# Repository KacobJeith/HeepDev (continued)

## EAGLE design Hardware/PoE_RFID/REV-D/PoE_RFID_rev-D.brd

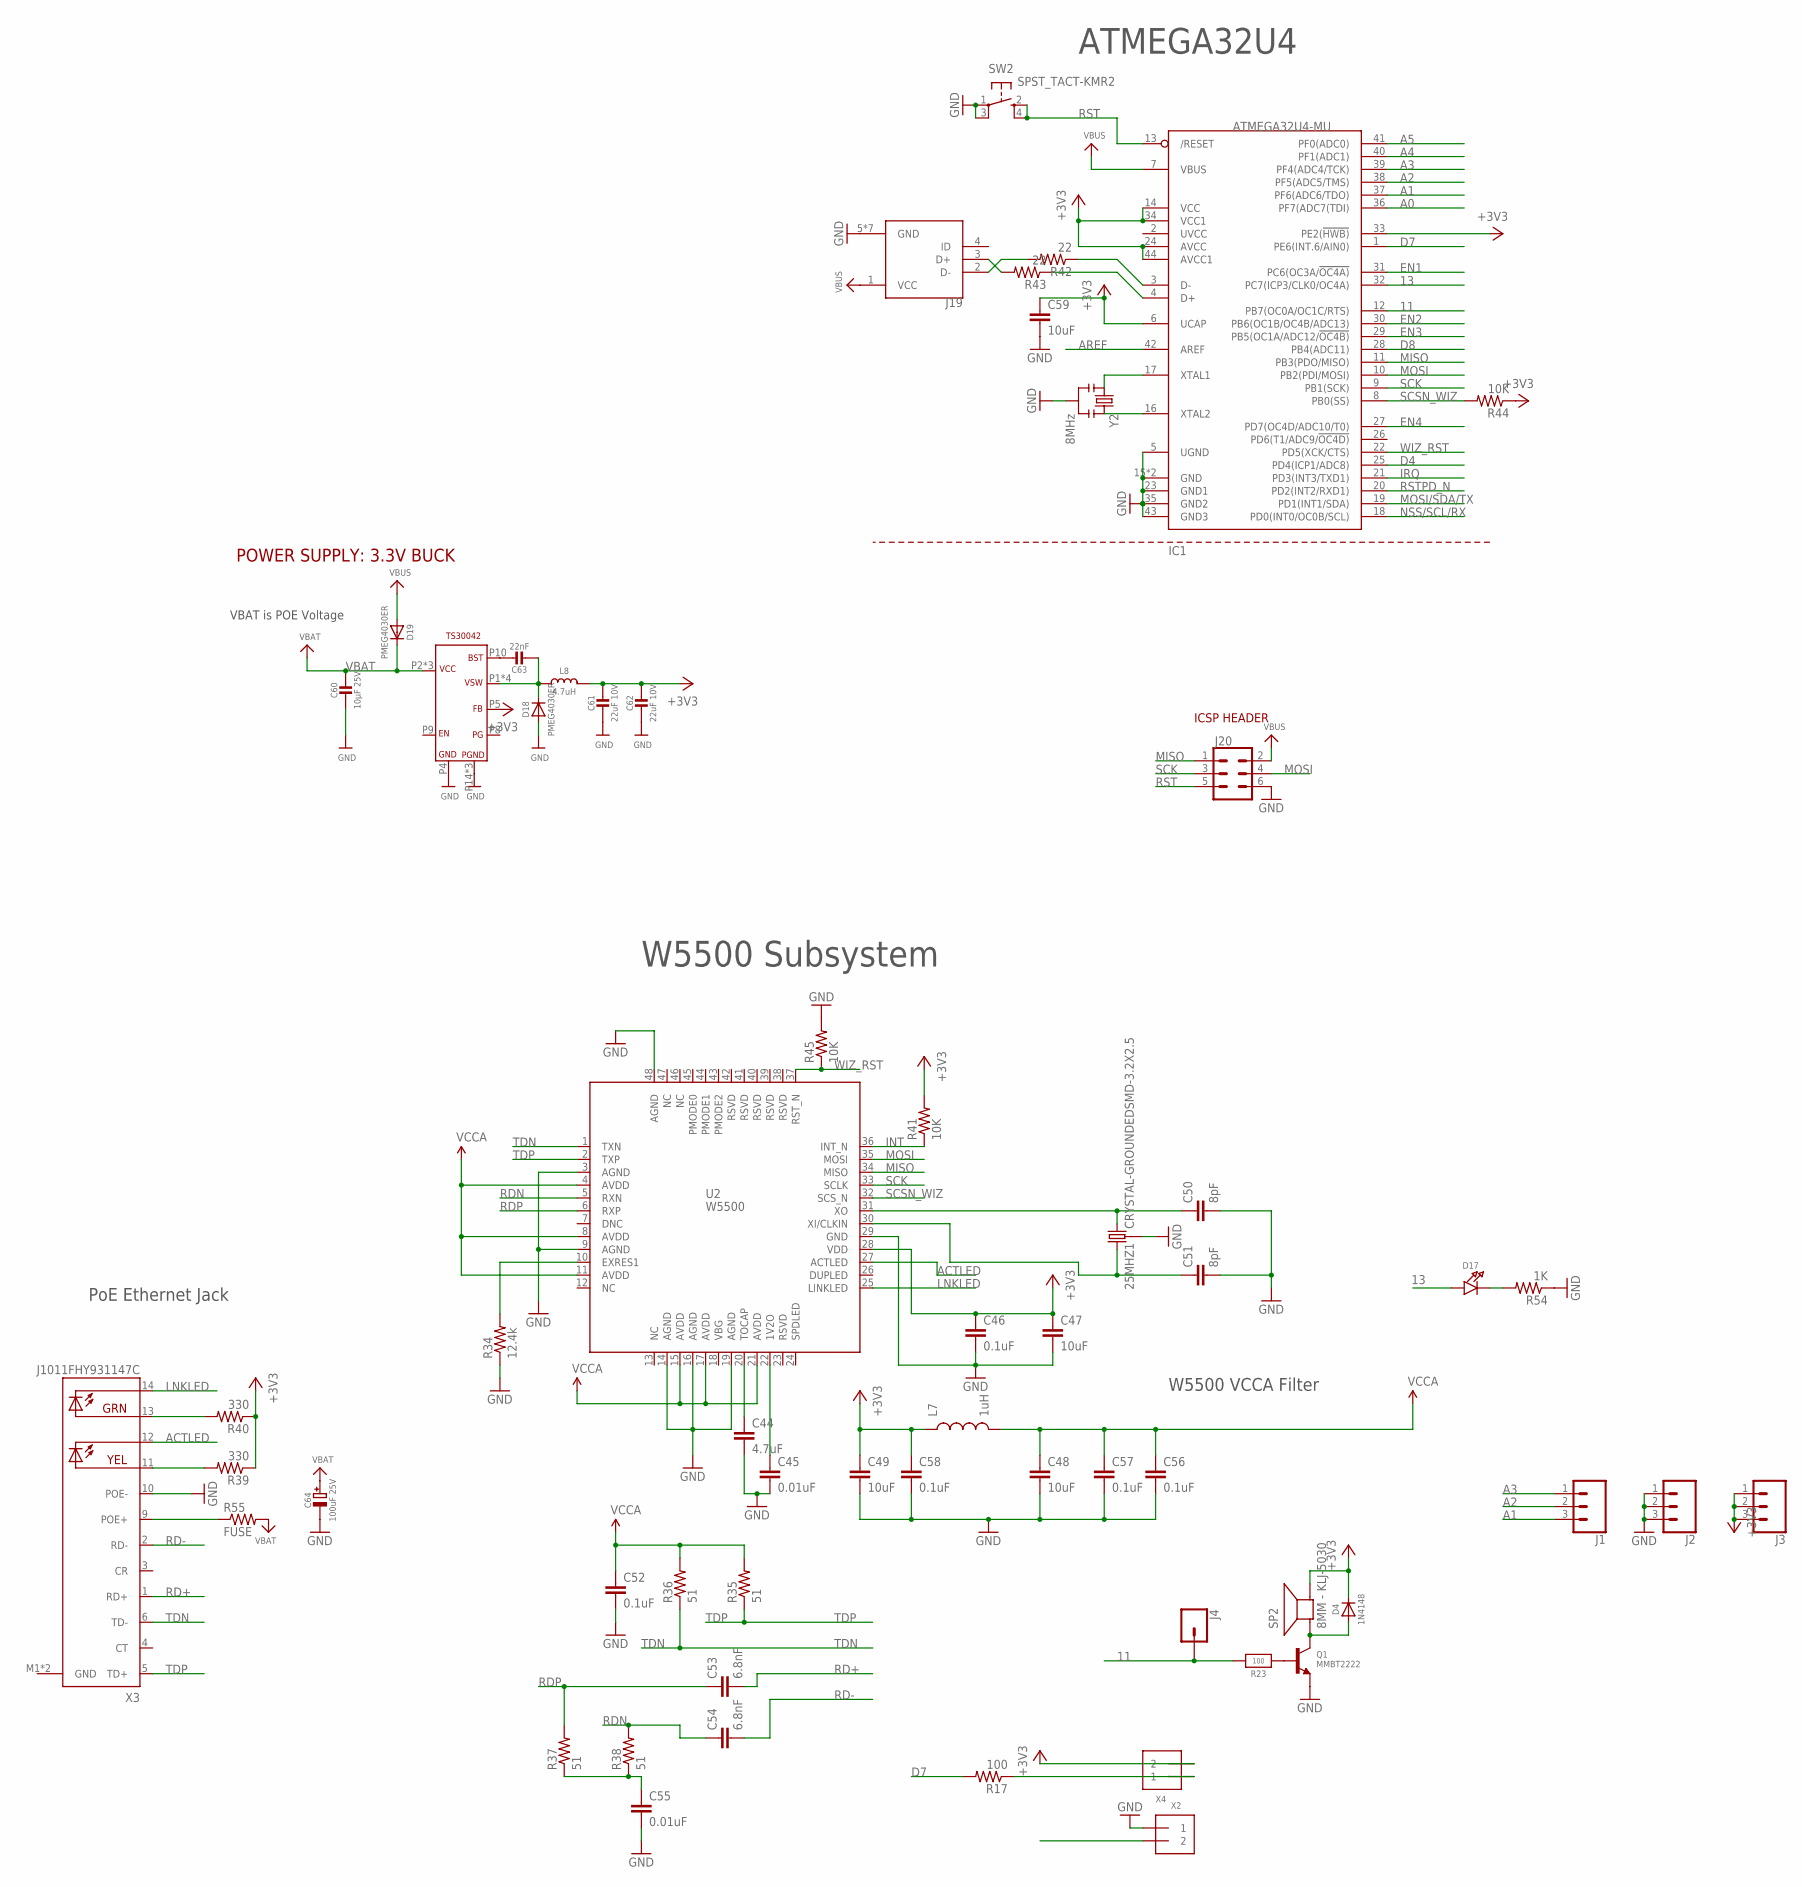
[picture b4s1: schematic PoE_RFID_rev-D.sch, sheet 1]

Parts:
25MHZ1: CRYSTAL-GROUNDEDSMD-3.2X2.5; CRYSTAL-SMD-3.2X2.5MM
C44: 4.7uF; 0603-CAP
C45, C55: 0.01uF; 0603-CAP
C46, C52, C56, C57, C58: 0.1uF; 0603-CAP
C47, C48, C49, C59: 10uF; 0603-CAP
C50, C51: 8pF; 0603-CAP
C53, C54: 6.8nF; 0603-CAP
C60: 10µF 25V; 0603-MINI
C61, C62: 22uF 10V; 0603-MINI
C63: 22nF; 0603-MINI
C64: 100uF 25V; PANASONIC_D
D4: 1N4148; SOD-323
D17: LED0805_NOOUTLINE; CHIPLED_0805_NOOUTLINE
D18, D19: PMEG4030ER; SOD-123
IC1: ATMEGA32U4-MU; TQFN44_7MM
J1: CONN_031X03_NO_SILK; 1X03_NO_SILK
J2, J3: CONN_03; 1X03
J4: CONN_01; 1X01
J19: 10103594-0001LF; FCI_10103594-0001LF
J20: CONN_03X2NO_SILK; 2X3-NS
L7: 1uH; 0603
L8: 4.7uH; INDUCTOR_5X5MM_TDK_VLC5045
Q1: MMBT2222; SOT23-WIDE
R17: 100; 0603-RES
R23: 100; 0603-NO@1
R34: 12.4k; 0603-RES
R35, R36, R37, R38: 51; 0603-RES
R39, R40: 330; 0603-RES
R41, R44, R45: 10K; 0603-RES
R42, R43: 22; 0603-RES
R54: 1K; 0603-RES
R55: FUSE; 0603-RES
SP2: 8MM - KLJ-5030; BUZZER_SMT_5MM
SW2: SPST_TACT-KMR2; KMR2
U2: W5500
U$55: BUCK_CONVERTER; QFN-16
X2, X4: TERMBLOCK_1X2; TERMBLOCK_1X2-3.5MM
X3: J1011FHY931147C; HANRUN_POE
Y2: 8MHz; RESONATOR-SMD

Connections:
11: IC1.12 (PB7(OC0A/OC1C/RTS)), J4.1, R23.2
13: D17.A, IC1.32 (PC7(ICP3/CLK0/OC4A))
+3V3: C46.1, C47.1, C49.1, C58.1, C59.1, C61.1, C62.1, D4.C, IC1.6 (UCAP), IC1.14 (VCC), IC1.24 (AVCC), IC1.33 (PE2(!HWB)), IC1.34 (VCC1), IC1.44 (AVCC1), J3.1, J3.2, J3.3, L7.1, L8.P$2 (2), R39.1, R40.1, R41.2, R44.1, SP2.-, U2.28 (VDD), U$55.P5 (FB), X2.2; also elsewhere on the board
A0: IC1.36 (PF7(ADC7(TDI))
A1: IC1.37 (PF6(ADC6/TDO)), J1.3
A2: IC1.38 (PF5(ADC5/TMS)), J1.2
A3: IC1.39 (PF4(ADC4/TCK)), J1.1
A4: IC1.40 (PF1(ADC1))
A5: IC1.41 (PF0(ADC0))
ACTLED: U2.27 (ACTLED), X3.12 (YEL-C)
AREF: IC1.42 (AREF)
D4: IC1.25 (PD4(ICP1/ADC8))
D7: IC1.1 (PE6(INT.6/AIN0)), R17.2
D8: IC1.28 (PB4(ADC11))
D+1: IC1.4 (D+), R43.1
D-1: IC1.3 (D-), R42.1
EN1: IC1.31 (PC6(OC3A/!OC4A)), X4.2
EN2: IC1.30 (PB6(OC1B/OC4B/ADC13))
EN3: IC1.29 (PB5(OC1A/ADC12/!OC4B))
EN4: IC1.27 (PD7(OC4D/ADC10/T0))
GND: 25MHZ1.2 (3), 25MHZ1.4 (3), C44.2, C45.2, C46.2, C47.2, C48.2, C49.2, C50.2, C51.2, C52.2, C55.2, C56.2, C57.2, C58.2, C59.2, C60.2, C61.2, C62.2, C64.-, D18.A, IC1.5 (UGND), IC1.15 (GND), IC1.23 (GND1), IC1.35 (GND2), IC1.43 (GND3), IC1.THERMAL (GND), J2.1, J2.2, J2.3, J19.5 (GND), J19.P1 (GND), J19.P2 (GND), J19.P3 (GND), J19.P4 (GND), J19.P5 (GND), J19.P6 (GND), J20.6, Q1.2 (E), R34.1, R45.2, R54.1, SW2.1, SW2.3 (P1), U2.3 (AGND), U2.9 (AGND), U2.14 (AGND), U2.16 (AGND), U2.19 (AGND), U2.29 (GND), U2.48 (AGND), U$55.P4 (GND), U$55.P14 (PGND), U$55.P15 (PGND), U$55.PAD (PGND), X3.10 (POE-), X3.M1 (GND), X3.M2 (GND), X4.1, Y2.2; also elsewhere on the board
INT: R41.1, U2.36 (INT_N)
IRQ: IC1.21 (PD3(INT3/TXD1)); also elsewhere on the board
LNKLED: U2.25 (LINKLED), X3.14 (GRN-C)
MISO: IC1.11 (PB3(PDO/MISO)), J20.1, U2.34 (MISO)
MOSI: IC1.10 (PB2(PDI/MOSI)), J20.4, U2.35 (MOSI)
MOSI/SDA/TX: IC1.19 (PD1(INT1/SDA)); also elsewhere on the board
unnamed: R17.1, X2.1
unnamed: Q1.1 (B), R23.1
unnamed: D4.A, Q1.3 (C), SP2.+
unnamed: C44.1, U2.20 (TOCAP)
unnamed: C45.1, U2.22 (1V2O)
unnamed: R34.2, U2.10 (EXRES1)
unnamed: C55.1, R37.1, R38.1
unnamed: 25MHZ1.3 (2), C50.1, U2.31 (XO)
unnamed: 25MHZ1.1, C51.1, U2.30 (XI/CLKIN)
unnamed: IC1.16 (XTAL2), Y2.3
unnamed: IC1.17 (XTAL1), Y2.1
unnamed: J19.3 (D+), R43.2
unnamed: J19.2 (D-), R42.2
unnamed: D17.C, R54.2
unnamed: R40.2, X3.13 (GRN-A)
unnamed: R39.2, X3.11 (YEL-A)
unnamed: C63.1, U$55.P10 (BST)
unnamed: C63.2, D18.C, L8.P$1 (1), U$55.P1 (VSW), U$55.P12 (VSW), U$55.P13 (VSW), U$55.P16 (VSW)
unnamed: R55.1, X3.9 (POE+)
NSS/SCL/RX: IC1.18 (PD0(INT0/OC0B/SCL)); also elsewhere on the board
RD+: C53.2, X3.1 (RD+)
RD-: C54.2, X3.2 (RD-)
RDN: C54.1, R38.2, U2.5 (RXN)
RDP: C53.1, R37.2, U2.6 (RXP)
RST: IC1.13 (/RESET), J20.5, SW2.2 (S), SW2.4 (S1)
RSTPD_N: IC1.20 (PD2(INT2/RXD1)); also elsewhere on the board
SCK: IC1.9 (PB1(SCK)), J20.3, U2.33 (SCLK)
SCSN_WIZ: IC1.8 (PB0(SS)), R44.2, U2.32 (SCS_N)
TDN: R36.1, U2.1 (TXN), X3.6 (TD-)
TDP: R35.1, U2.2 (TXP), X3.5 (TD+)
VBAT: C60.1, C64.+, D19.C, R55.2, U$55.P2 (VCC), U$55.P3 (VCC), U$55.P11 (VCC)
VBUS: D19.A, IC1.7 (VBUS), J19.1 (VCC), J20.2
VCCA: C48.1, C52.1, C56.1, C57.1, L7.2, R35.2, R36.2, U2.4 (AVDD), U2.8 (AVDD), U2.11 (AVDD), U2.15 (AVDD), U2.17 (AVDD), U2.21 (AVDD)
WIZ_RST: IC1.22 (PD5(XCK/CTS)), R45.1, U2.37 (RST_N)

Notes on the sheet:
W5500 Subsystem
W5500 VCCA Filter
PoE Ethernet Jack
ATMEGA32U4
ICSP HEADER
POWER SUPPLY: 3.3V BUCK
VBAT is POE Voltage

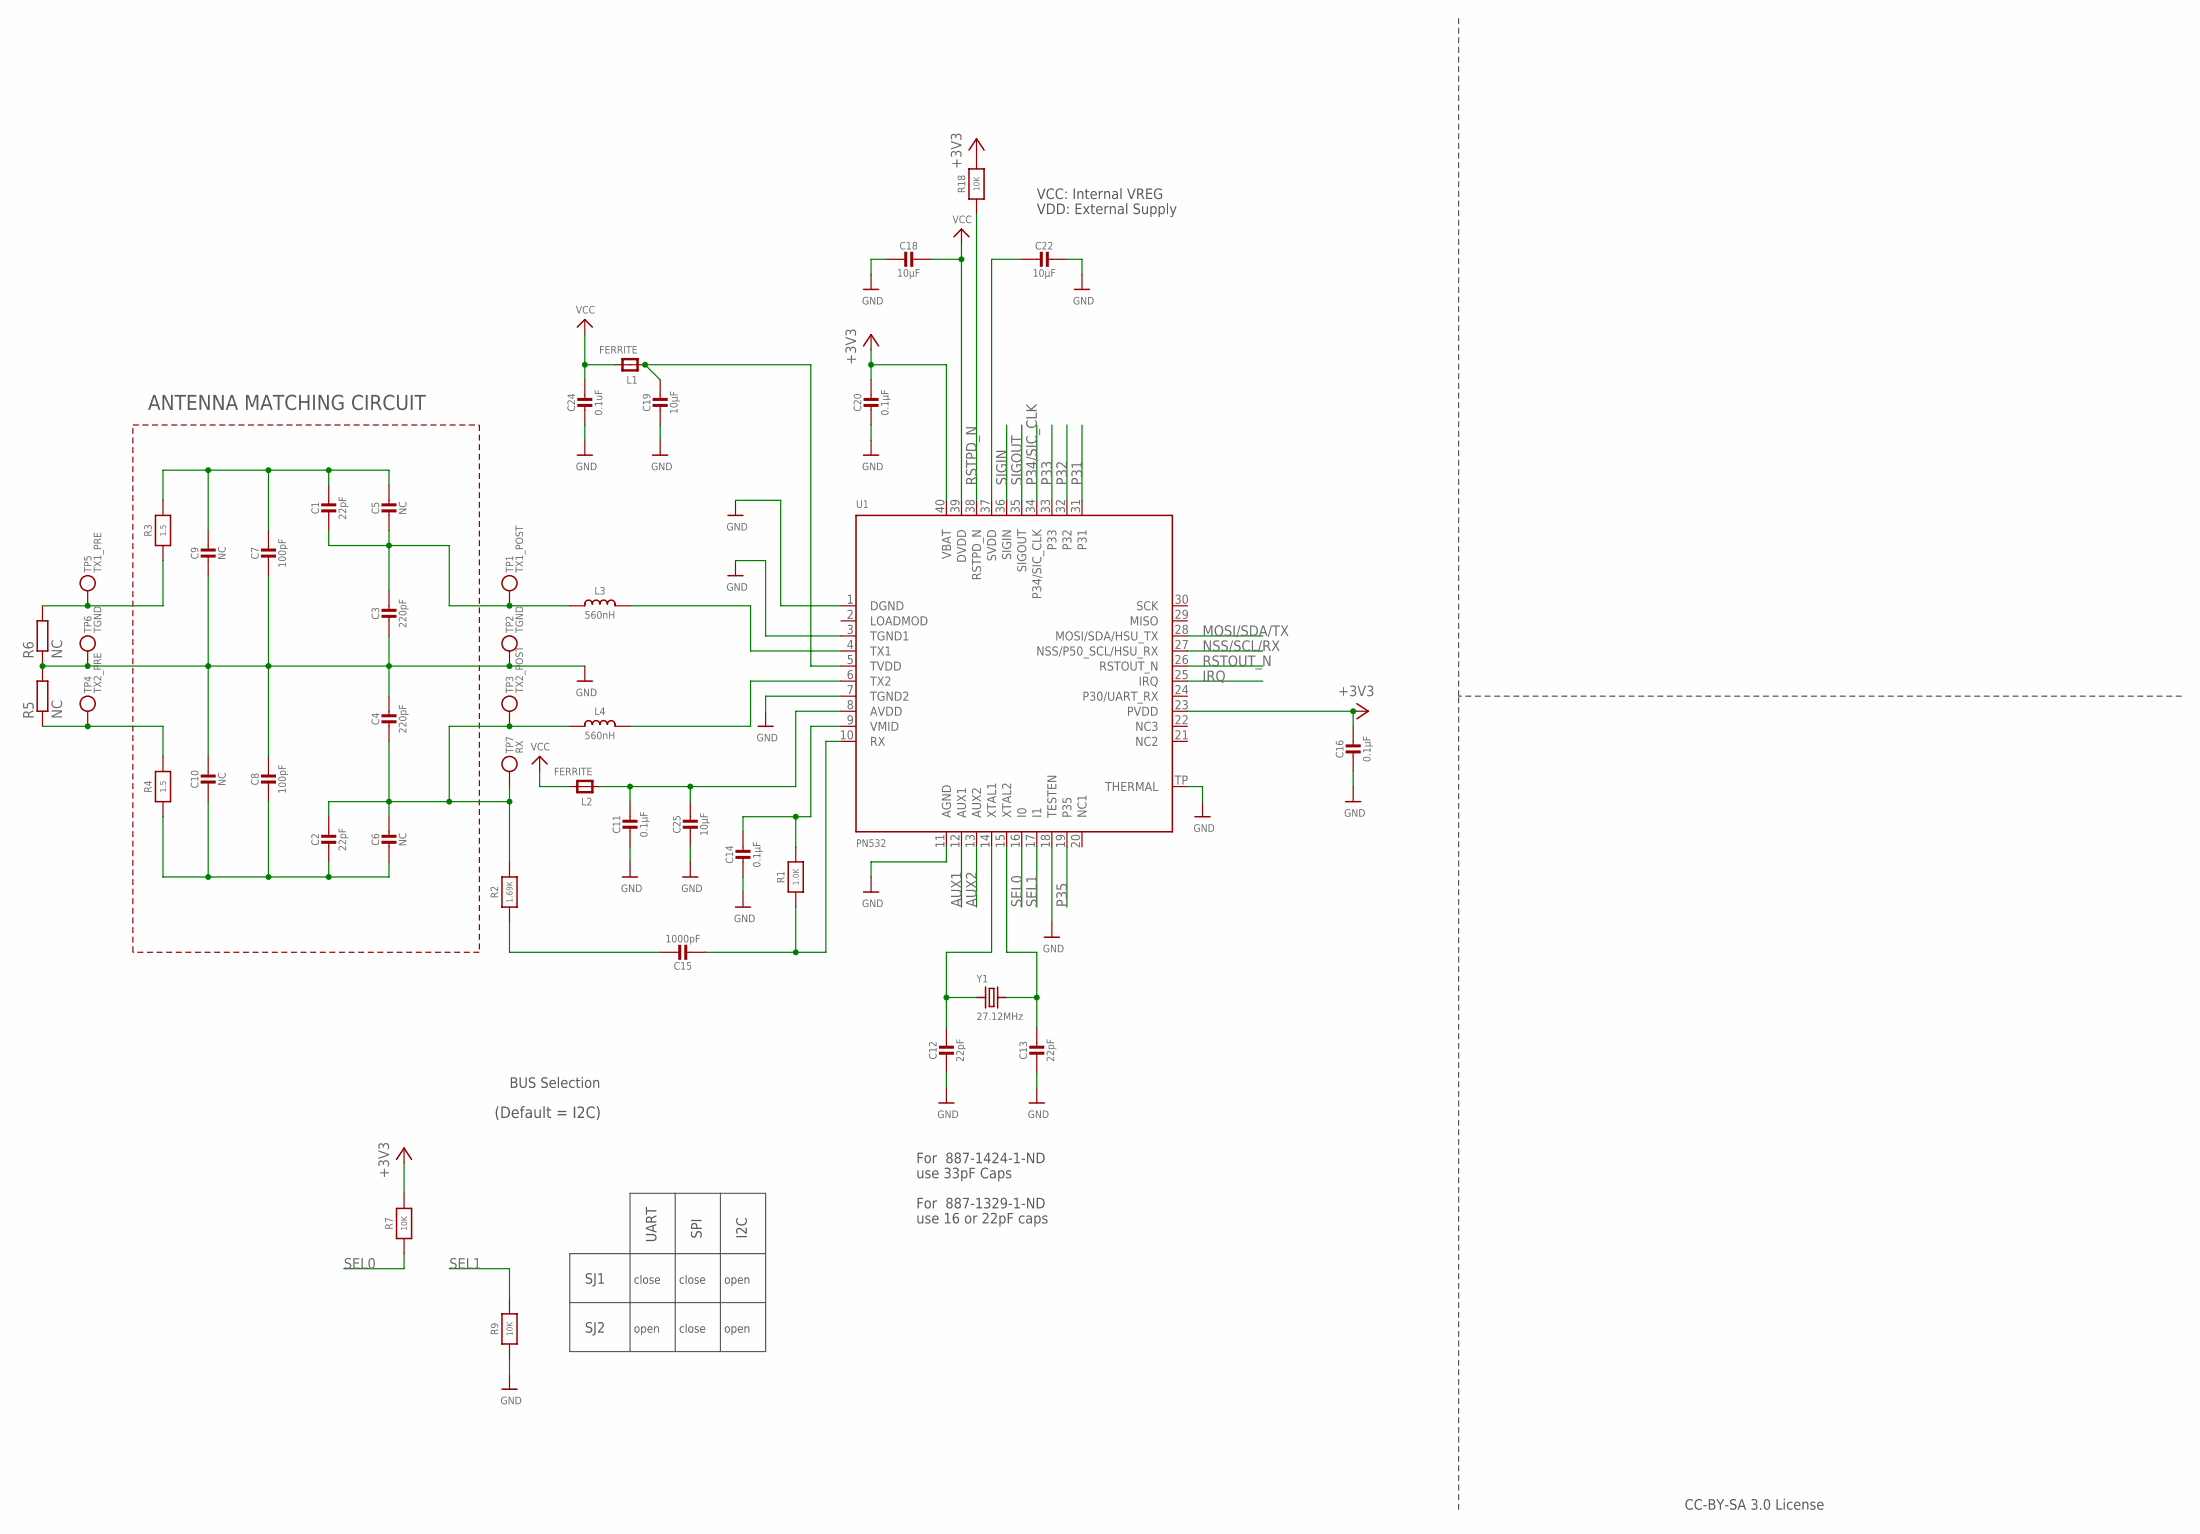
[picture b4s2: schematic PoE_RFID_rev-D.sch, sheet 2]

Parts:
C1, C2, C12, C13: 22pF; 0603-NO
C3, C4: 220pF; 0603-NO
C5, C6, C9, C10: NC; 0603-NO
C7, C8: 100pF; 0603-NO
C11, C14, C16, C20: 0.1µF; 0603-NO
C15: 1000pF; 0603-NO
C18, C19, C22, C25: 10µF; 0603-NO
C24: 0.1uF; 0603-NO
L1, L2: FERRITE; _0603
L3, L4: 560nH; 0603-NO
R1: 1.0K; 0603-NO@1
R2: 1.69K; 0603-NO@1
R3, R4: 1.5; 0603-NO@1
R5, R6: NC; R0201
R7, R9, R18: 10K; 0603-NO@1
TP1: TX1_POST; PAD-1.5X2.0
TP2, TP6: TGND; PAD-1.5X2.0
TP3: TX2_POST; PAD-1.5X2.0
TP4: TX2_PRE; PAD-1.5X2.0
TP5: TX1_PRE; PAD-1.5X2.0
TP7: RX; PAD-1.5X2.0
U1: PN532; HVQFN40-6X6
Y1: 27.12MHz; CRYSTAL_3.2X2.5

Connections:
+3V3: C16.1, C20.1, R7.2, R18.2, U1.23 (PVDD), U1.40 (VBAT); also elsewhere on the board
AUX1: U1.12 (AUX1)
AUX2: U1.13 (AUX2)
GND: C3.2, C4.1, C7.2, C8.1, C9.2, C10.1, C11.2, C12.2, C13.2, C14.2, C16.2, C18.2, C19.2, C20.2, C22.1, C24.2, C25.2, R5.2, R6.1, R9.1, TP2.P$1, TP6.P$1, U1.1 (DGND), U1.3 (TGND1), U1.7 (TGND2), U1.11 (AGND), U1.18 (TESTEN), U1.TP (THERMAL); also elsewhere on the board
IRQ: U1.25 (IRQ); also elsewhere on the board
MOSI/SDA/TX: U1.28 (MOSI/SDA/HSU_TX); also elsewhere on the board
unnamed: L3.2, U1.4 (TX1)
unnamed: L4.2, U1.6 (TX2)
unnamed: C1.2, C3.1, C5.2, L3.1, TP1.P$1
unnamed: R3.1, R6.2, TP5.P$1
unnamed: R4.2, R5.1, TP4.P$1
unnamed: C12.1, U1.14 (XTAL1), Y1.1
unnamed: C13.1, U1.15 (XTAL2), Y1.2
unnamed: C15.1, R2.1
unnamed: C14.1, R1.2, U1.9 (VMID)
unnamed: C15.2, R1.1, U1.10 (RX)
unnamed: C2.1, C4.2, C6.1, L4.1, R2.2, TP3.P$1, TP7.P$1
unnamed: C11.1, C25.1, L2.1, U1.8 (AVDD)
unnamed: C19.1, L1.1, U1.5 (TVDD)
unnamed: C22.2, U1.37 (SVDD)
NSS/SCL/RX: U1.27 (NSS/P50_SCL/HSU_RX); also elsewhere on the board
P31: U1.31
P32: U1.32
P33: U1.33
P34/SIC_CLK: U1.34 (P34/SIC_CLK)
P35: U1.19 (P35)
RSTOUT_N: U1.26 (RSTOUT_N)
RSTPD_N: R18.1, U1.38 (RSTPD_N); also elsewhere on the board
SEL0: R7.1, U1.16 (I0)
SEL1: R9.2, U1.17 (I1)
SIGIN: U1.36 (SIGIN)
SIGOUT: U1.35 (SIGOUT)
TX1_ANTENNA: C1.1, C5.1, C7.1, C9.1, R3.2
TX2_ANTENNA: C2.2, C6.2, C8.2, C10.2, R4.1
VCC: C18.1, C24.1, L1.2, L2.2, U1.39 (DVDD)

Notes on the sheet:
ANTENNA MATCHING CIRCUIT
SJ1
SJ2
UART
SPI
I2C
close
open
CC-BY-SA 3.0 License
For 887-1329-1-ND
use 16 or 22pF caps
For 887-1424-1-ND
use 33pF Caps
BUS Selection
(Default = I2C)
VCC: Internal VREG
VDD: External Supply

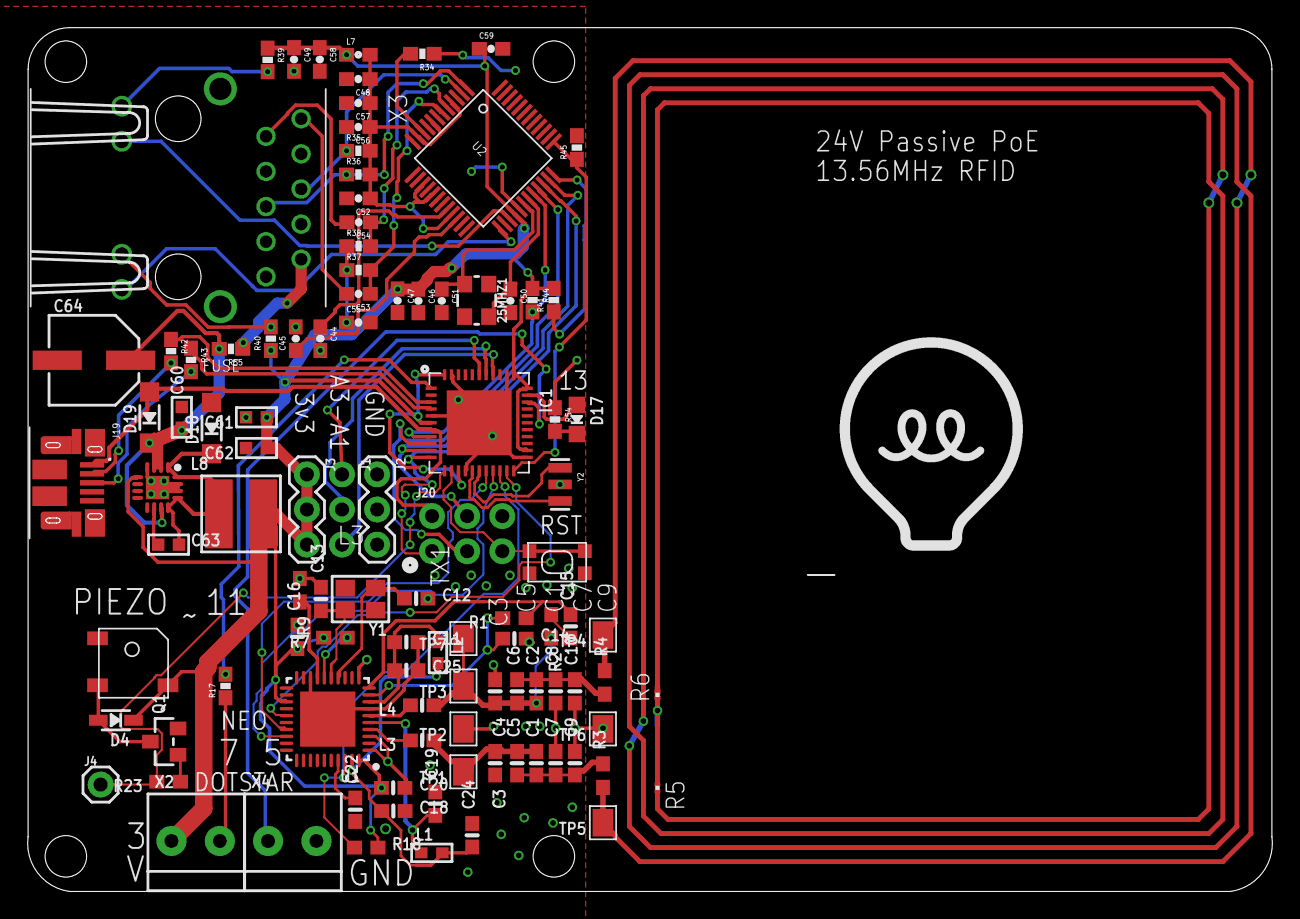
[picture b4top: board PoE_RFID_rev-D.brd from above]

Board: 2 copper layers, 90.0 x 62.5 mm, 105 parts (0 on the bottom side), 71 nets.

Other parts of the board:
U$19: HEEPLOGO

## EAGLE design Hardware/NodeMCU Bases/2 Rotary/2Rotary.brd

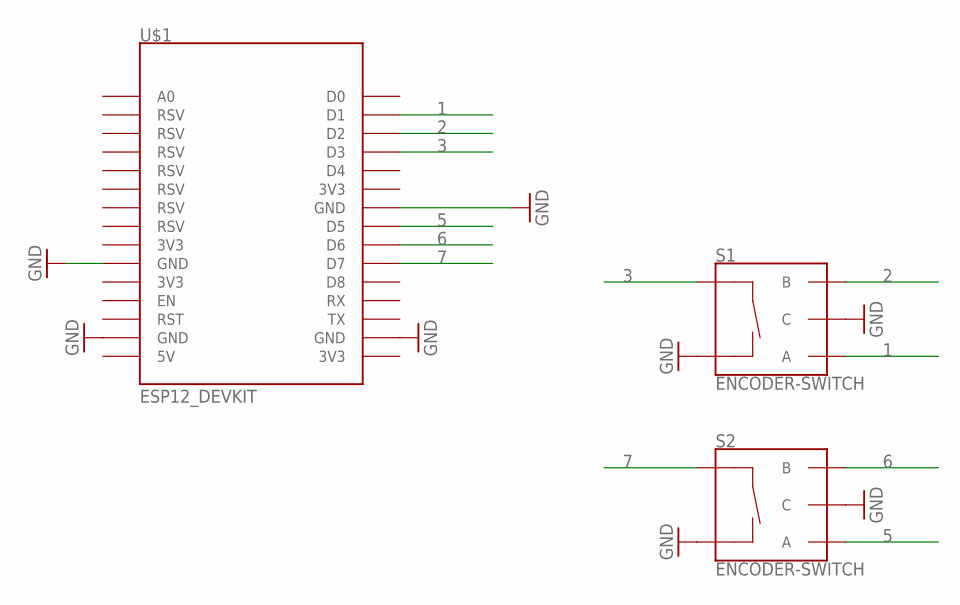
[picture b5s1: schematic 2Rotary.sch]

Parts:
S1, S2: ENCODER-SWITCH; ROTARY_ENC_PLAIN
U$1: ESP12_DEVKIT

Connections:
1: S1.A, U$1.D1
2: S1.B, U$1.D2
3: S1.SW+, U$1.D3
5: S2.A, U$1.D5
6: S2.B, U$1.D6
7: S2.SW+, U$1.D7
GND: S1.C, S1.SW-, S2.C, S2.SW-, U$1.GND@0 (GND), U$1.GND@1 (GND), U$1.GND@2 (GND), U$1.GND@3 (GND)

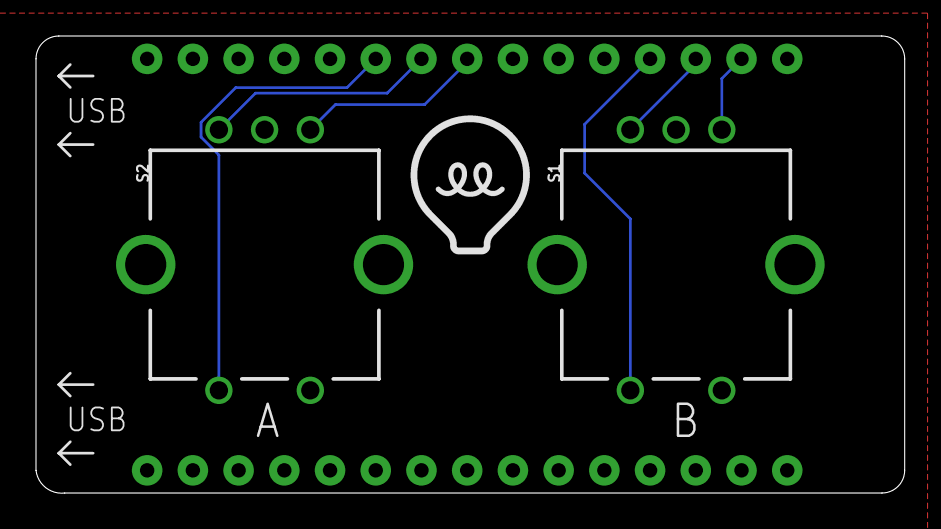
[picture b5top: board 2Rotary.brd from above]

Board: 2 copper layers, 48.3 x 25.4 mm, 4 parts (1 on the bottom side), 7 nets.

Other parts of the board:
U$2: HEEPLOGOSMALL

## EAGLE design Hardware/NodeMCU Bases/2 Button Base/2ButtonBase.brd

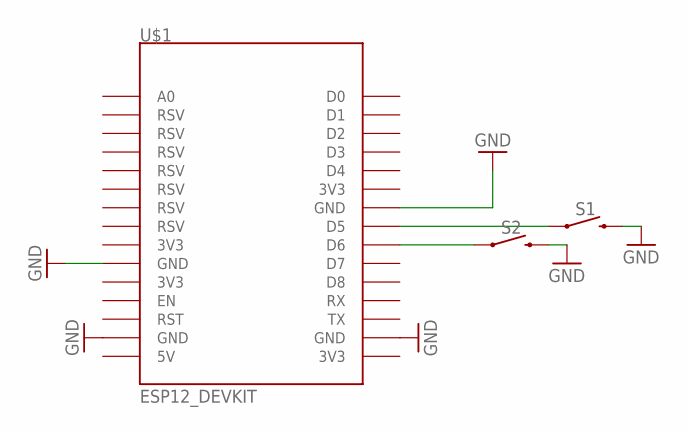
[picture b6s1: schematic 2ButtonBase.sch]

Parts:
S1, S2: MOMENTARY-SWITCH-SPST-PTH-12MM; TACTILE_SWITCH_PTH_12MM
U$1: ESP12_DEVKIT

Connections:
GND: S1.3 (2), S2.3 (2), U$1.GND@0 (GND), U$1.GND@1 (GND), U$1.GND@2 (GND), U$1.GND@3 (GND)
unnamed: S1.1, U$1.D5
unnamed: S2.1, U$1.D6

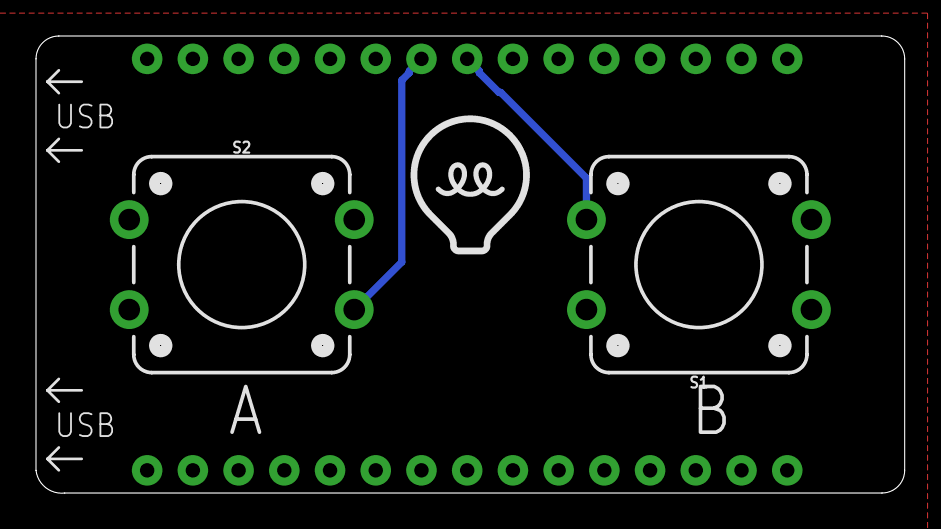
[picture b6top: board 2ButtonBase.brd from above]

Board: 2 copper layers, 48.3 x 25.4 mm, 4 parts (1 on the bottom side), 3 nets.

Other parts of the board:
U$2: HEEPLOGOSMALL

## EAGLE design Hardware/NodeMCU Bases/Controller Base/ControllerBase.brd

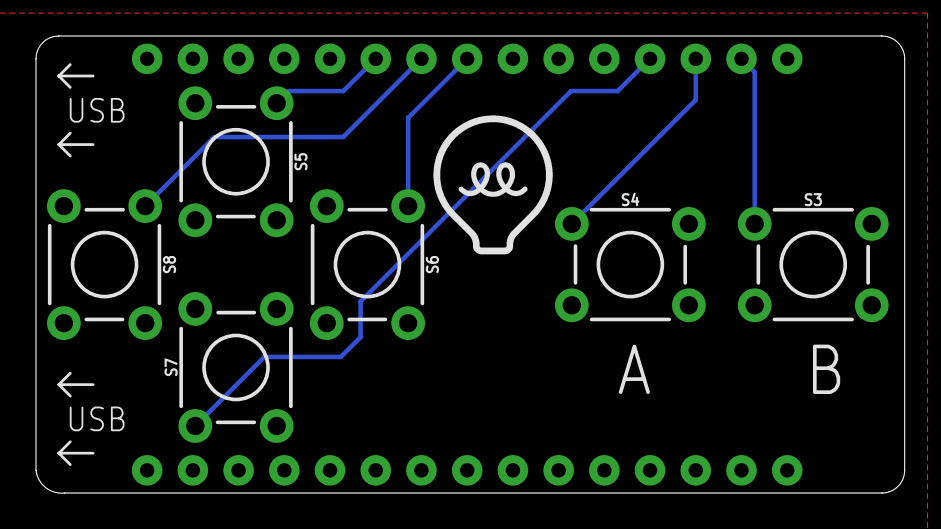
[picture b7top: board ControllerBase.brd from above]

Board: 2 copper layers, 48.3 x 25.4 mm, 8 parts (1 on the bottom side), 7 nets.

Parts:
S3, S4, S5, S6, S7, S8: TACTILE_SWITCH_PTH_6.0MM
U$1: ESP12_DEVKIT
U$2: HEEPLOGOSMALL

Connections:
1: S3.1, U$1.D1
2: S4.1, U$1.D2
3: S7.1, U$1.D3
5: S6.1, U$1.D5
6: S8.1, U$1.D6
7: S5.1, U$1.D7
GND: S3.3, S4.3, S5.3, S6.3, S7.3, S8.3, U$1.GND@0, U$1.GND@1, U$1.GND@2, U$1.GND@3

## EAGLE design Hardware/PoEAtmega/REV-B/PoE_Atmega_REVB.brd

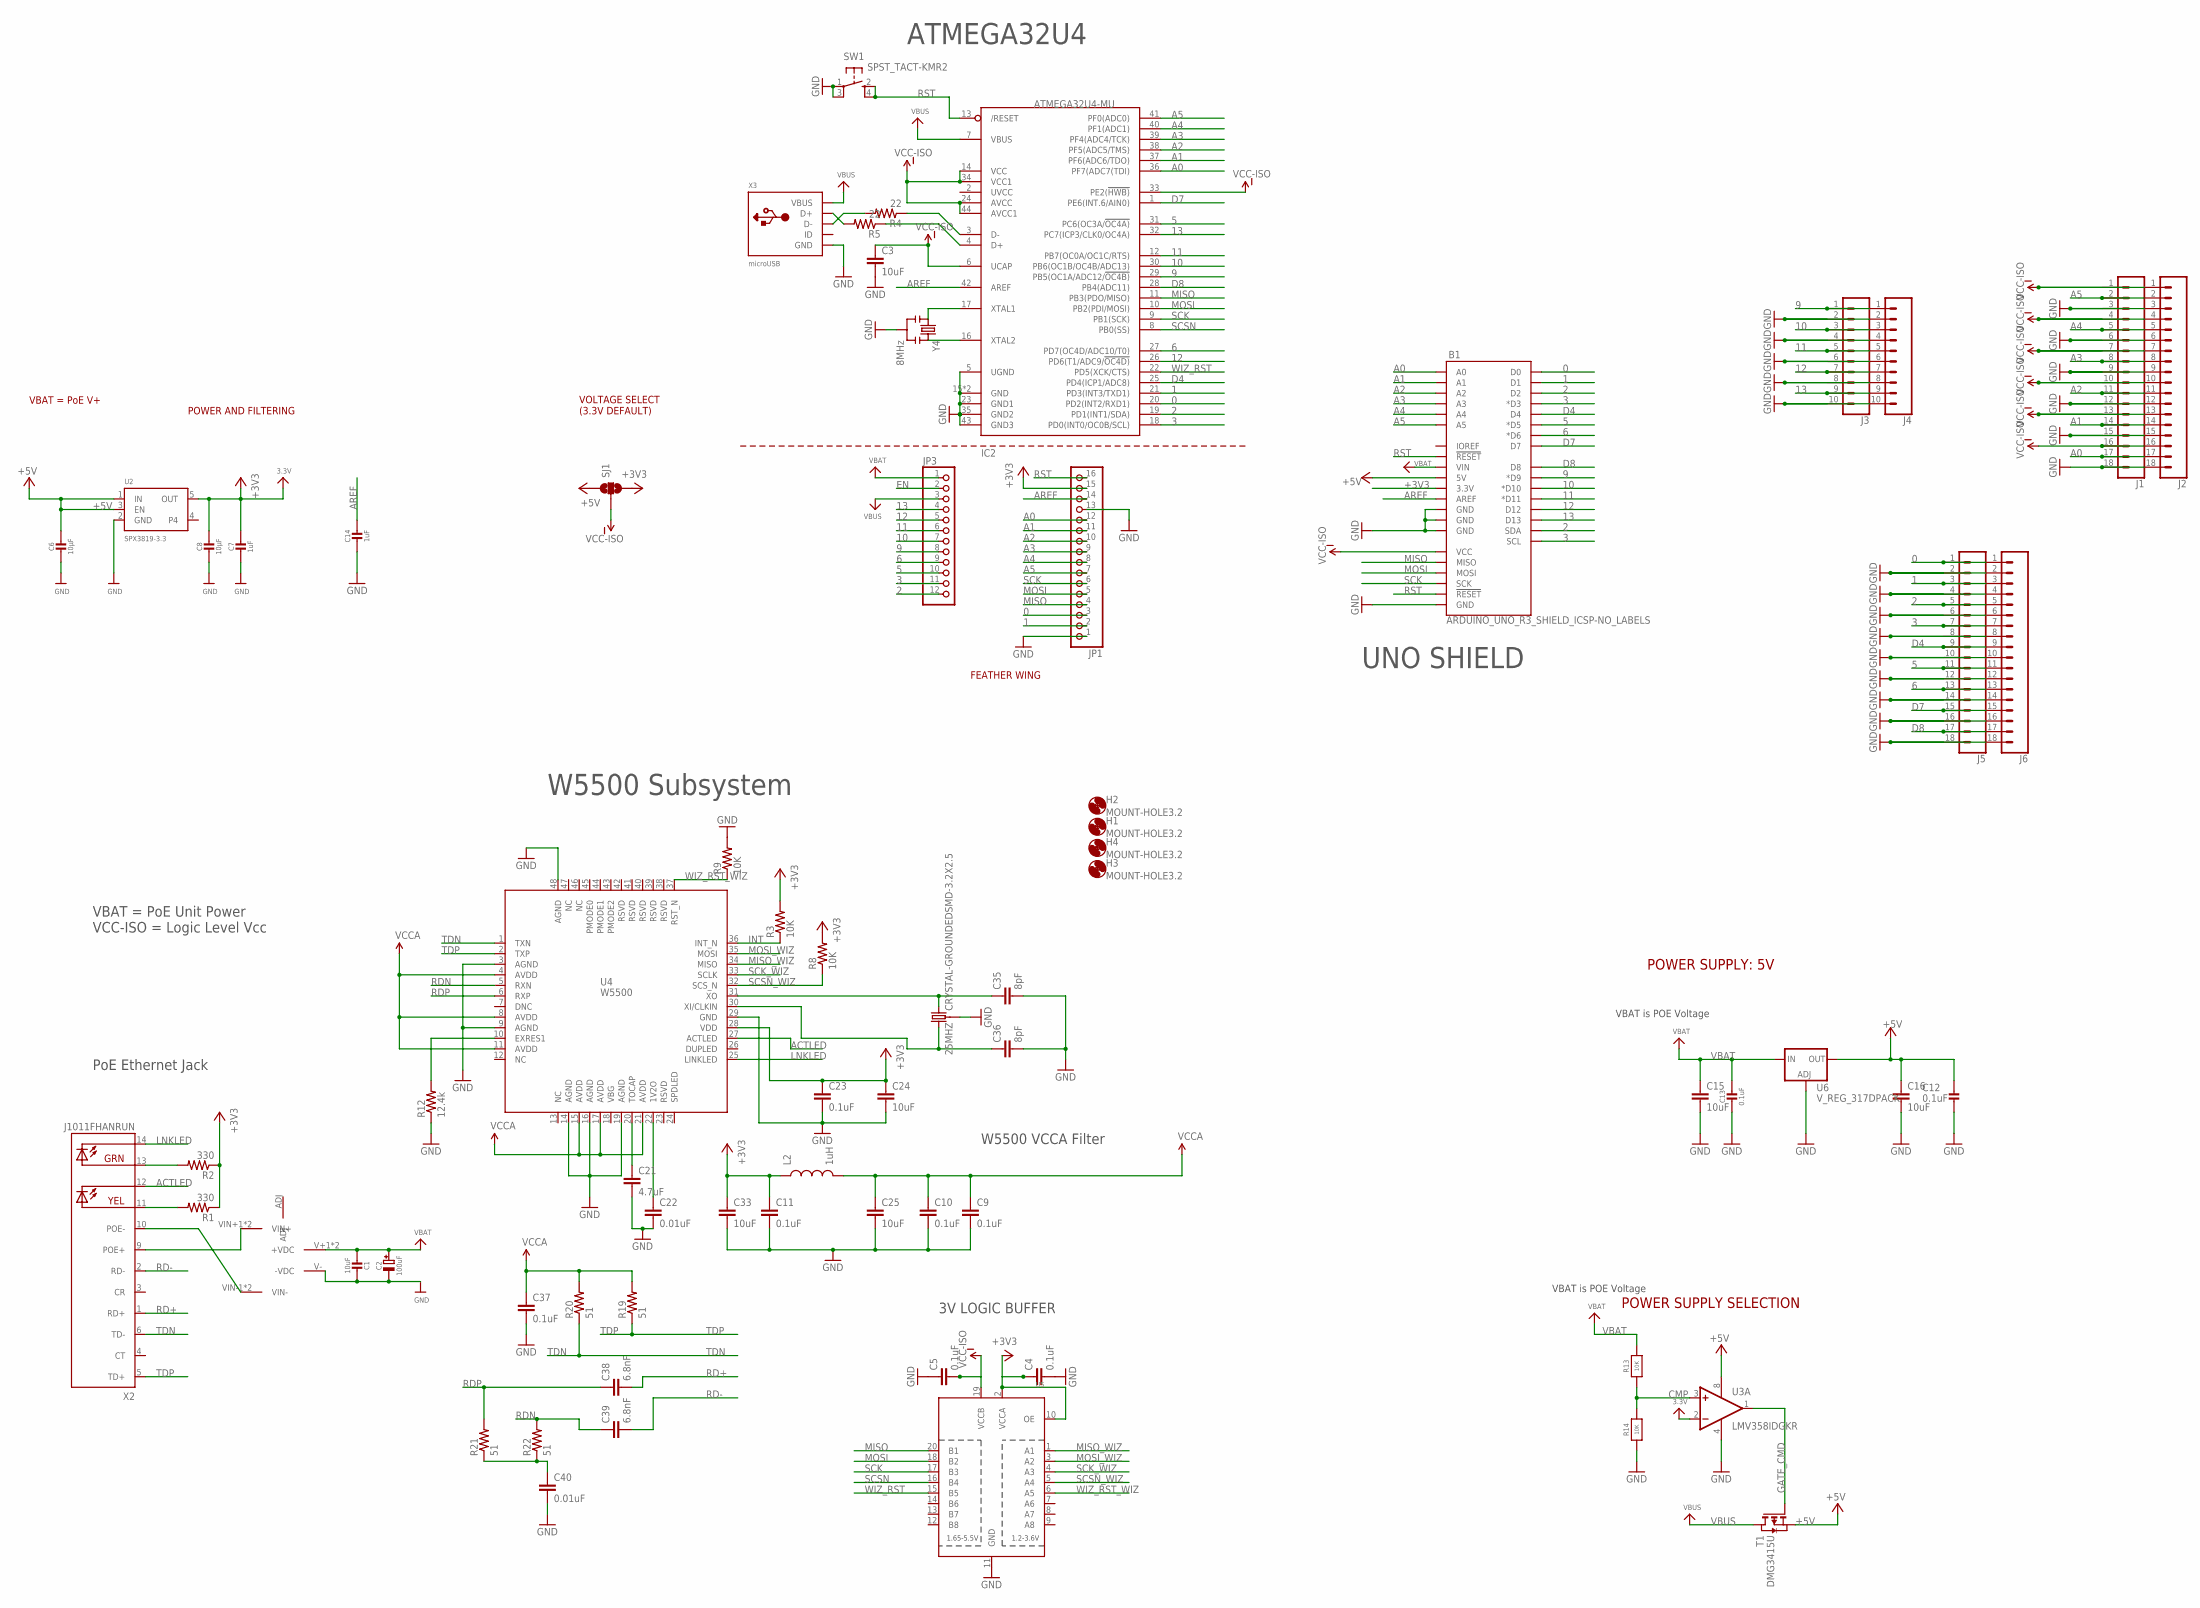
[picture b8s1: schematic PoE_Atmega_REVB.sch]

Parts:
25MHZ: CRYSTAL-GROUNDEDSMD-3.2X2.5; CRYSTAL-SMD-3.2X2.5MM
B1: ARDUINO_UNO_R3_SHIELD_ICSP-NO_LABELS; UNO_R3_SHIELD_ICSP_NOLABELS
C1: 10uF; _0805MP
C2: 100uF; PANASONIC_C
C3, C15, C16, C24, C25, C33: 10uF; 0603-CAP
C4, C5, C9, C10, C11, C23, C37: 0.1uF; 0603-CAP
C6, C8: 10µF; 0603-MINI
C7: 1uF; 0603-MINI
C12, C13: 0.1uF; 0805-NO
C14: 1uF; 0603-NO
C21: 4.7uF; 0603-CAP
C22, C40: 0.01uF; 0603-CAP
C35, C36: 8pF; 0603-CAP
C38, C39: 6.8nF; 0603-CAP
H1, H2, H3, H4: MOUNT-HOLE3.2; 3,2
IC2: ATMEGA32U4-MU; TQFN44_7MM
J1, J2, J5, J6: CONN_18; 1X18
J3, J4: CONN_10"; 1X10
JP1: HEADER-1X16ROUND; 1X16_ROUND
JP3: HEADER-1X12; 1X12_ROUND
L2: 1uH; 0603
R1, R2: 330; 0603-RES
R3, R8, R9: 10K; 0603-RES
R4, R5: 22; 0603-RES
R12: 12.4k; 0603-RES
R13, R14: 10K; 0805-NO
R19, R20, R21, R22: 51; 0603-RES
SJ1: SOLDERJUMPER_2WAYPASTE2&3; SJ_3_PASTE2&3
SW1: SPST_TACT-KMR2; KMR2
T1: DMG3415U; SOT-23
U2: SPX3819-3.3; SOT23-5
U3: LMV358IDGKR; MSOP08
U4: W5500
U5: TXB0108PWR; TSSOP20
U6: V_REG_317DPACK; V-REG_DPACK
U$1: SILVERTEL_POEMICRO; AG9900
X2: J1011FHANRUN; HANRUN_POE
X3: microUSB; 4UCONN_20329_V2
Y4: 8MHz; RESONATOR-SMD

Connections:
0: B1.RX (D0), IC2.20 (PD2(INT2/RXD1)), J5.1, J6.1, JP1.3
1: B1.TX (D1), IC2.21 (PD3(INT3/TXD1)), J5.3, J6.3, JP1.2
2: B1.D2, B1.SDA, IC2.19 (PD1(INT1/SDA)), J5.5, J6.5, JP3.12
3: B1.D3 (*D3), B1.SCL, IC2.18 (PD0(INT0/OC0B/SCL)), J5.7, J6.7, JP3.11
5: B1.D5 (*D5), IC2.31 (PC6(OC3A/!OC4A)), J5.11, J6.11, JP3.10
6: B1.D6 (*D6), IC2.27 (PD7(OC4D/ADC10/T0)), J5.13, J6.13, JP3.9
9: B1.D9 (*D9), IC2.29 (PB5(OC1A/ADC12/!OC4B)), J3.1, J4.1, JP3.8
10: B1.D10 (*D10), IC2.30 (PB6(OC1B/OC4B/ADC13)), J3.3, J4.3, JP3.7
11: B1.D11 (*D11), IC2.12 (PB7(OC0A/OC1C/RTS)), J3.5, J4.5, JP3.6
12: B1.D12, IC2.26 (PD6(T1/ADC9/!OC4D)), J3.7, J4.7, JP3.5
13: B1.D13, IC2.32 (PC7(ICP3/CLK0/OC4A)), J3.9, J4.9, JP3.4
+3V3: B1.3.3V, C4.1, C7.1, C8.1, C11.1, C23.1, C24.1, C33.1, JP1.15, L2.1, R1.1, R2.1, R3.2, R8.2, SJ1.3, U2.5 (OUT), U3.2 (-IN), U4.28 (VDD), U5.2 (VCCA), U5.10 (OE)
+5V: B1.5V, C6.1, C12.2, C16.1, SJ1.1, T1.2 (S), U2.1 (IN), U2.3 (EN), U3.8 (V+), U6.4 (OUT)
A0: B1.A0, IC2.36 (PF7(ADC7(TDI)), J1.17, J2.17, JP1.12
A1: B1.A1, IC2.37 (PF6(ADC6/TDO)), J1.14, J2.14, JP1.11
A2: B1.A2, IC2.38 (PF5(ADC5/TMS)), J1.11, J2.11, JP1.10
A3: B1.A3, IC2.39 (PF4(ADC4/TCK)), J1.8, J2.8, JP1.9
A4: B1.A4, IC2.40 (PF1(ADC1)), J1.5, J2.5, JP1.8
A5: B1.A5, IC2.41 (PF0(ADC0)), J1.2, J2.2, JP1.7
ACTLED: U4.27 (ACTLED), X2.12 (YEL-C)
AREF: B1.AREF, C14.1, IC2.42 (AREF), JP1.14
CMP: R13.1, R14.2, U3.3 (+IN)
D4: B1.D4, IC2.25 (PD4(ICP1/ADC8)), J5.9, J6.9
D7: B1.D7, IC2.1 (PE6(INT.6/AIN0)), J5.15, J6.15
D8: B1.D8, IC2.28 (PB4(ADC11)), J5.17, J6.17
D+: IC2.4 (D+), R5.1
D-: IC2.3 (D-), R4.1
EN: JP3.2
GATE_CMD: T1.3 (G), U3.1 (OUT)
GND: 25MHZ.2 (3), 25MHZ.4 (3), B1.GND@0 (GND), B1.GND@1 (GND), B1.GND@2 (GND), B1.GND_ICSP (GND), C1.1, C2.-, C3.2, C4.2, C5.1, C6.2, C7.2, C8.2, C9.2, C10.2, C11.2, C12.1, C13.2, C14.2, C15.2, C16.2, C21.2, C22.2, C23.2, C24.2, C25.2, C33.2, C35.2, C36.2, C37.2, C40.2, IC2.5 (UGND), IC2.15 (GND), IC2.23 (GND1), IC2.35 (GND2), IC2.43 (GND3), IC2.THERMAL (GND), J1.3, J1.6, J1.9, J1.12, J1.15, J1.18, J2.3, J2.6, J2.9, J2.12, J2.15, J2.18, J3.2, J3.4, J3.6, J3.8, J3.10, J4.2, J4.4, J4.6, J4.8, J4.10, J5.2, J5.4, J5.6, J5.8, J5.10, J5.12, J5.14, J5.16, J5.18, J6.2, J6.4, J6.6, J6.8, J6.10, J6.12, J6.14, J6.16, J6.18, JP1.1, JP1.13, R9.2, R12.1, R14.1, SW1.1, SW1.3 (P1), U2.2 (GND), U3.4 (V-), U4.3 (AGND), U4.9 (AGND), U4.14 (AGND), U4.16 (AGND), U4.19 (AGND), U4.29 (GND), U4.48 (AGND), U5.11 (GND), U6.1 (ADJ), U$1.V- (-VDC), X3.BASE@1 (GND), X3.BASE@2 (GND), X3.GND, X3.SPRT@1 (GND), X3.SPRT@2 (GND), X3.SPRT@3 (GND), X3.SPRT@4 (GND), Y4.2
INT: R3.1, U4.36 (INT_N)
LNKLED: U4.25 (LINKLED), X2.14 (GRN-C)
MISO: B1.MISO, IC2.11 (PB3(PDO/MISO)), JP1.4, U5.20 (B1)
MISO_WIZ: U4.34 (MISO), U5.1 (A1)
MOSI: B1.MOSI, IC2.10 (PB2(PDI/MOSI)), JP1.5, U5.18 (B2)
MOSI_WIZ: U4.35 (MOSI), U5.3 (A2)
unnamed: R5.2, X3.D+
unnamed: R1.2, X2.11 (YEL-A)
unnamed: R2.2, X2.13 (GRN-A)
unnamed: IC2.16 (XTAL2), Y4.3
unnamed: IC2.17 (XTAL1), Y4.1
unnamed: R4.2, X3.D-
unnamed: C21.1, U4.20 (TOCAP)
unnamed: C22.1, U4.22 (1V2O)
unnamed: R12.2, U4.10 (EXRES1)
unnamed: C40.1, R21.1, R22.1
unnamed: 25MHZ.3 (2), C35.1, U4.31 (XO)
unnamed: 25MHZ.1, C36.1, U4.30 (XI/CLKIN)
POE_VIN+: U$1.VIN+1 (VIN+), U$1.VIN+2 (VIN+), X2.9 (POE+)
POE_VIN-: U$1.VIN-1 (VIN-), U$1.VIN-2 (VIN-), X2.10 (POE-)
RD+: C38.2, X2.1 (RD+)
RD-: C39.2, X2.2 (RD-)
RDN: C39.1, R22.2, U4.5 (RXN)
RDP: C38.1, R21.2, U4.6 (RXP)
RST: B1.RES (!RESET!), B1.RST_ICSP (!RESET!), IC2.13 (/RESET), JP1.16, SW1.2 (S), SW1.4 (S1)
SCK: B1.SCK, IC2.9 (PB1(SCK)), JP1.6, U5.17 (B3)
SCK_WIZ: U4.33 (SCLK), U5.4 (A3)
SCSN: IC2.8 (PB0(SS)), U5.16 (B4)
SCSN_WIZ: R8.1, U4.32 (SCS_N), U5.5 (A4)
TDN: R20.1, U4.1 (TXN), X2.6 (TD-)
TDP: R19.1, U4.2 (TXP), X2.5 (TD+)
VBAT: B1.VIN, C1.2, C2.+, C13.1, C15.1, JP3.1, R13.2, U6.3 (IN), U$1.V+1 (+VDC), U$1.V+2 (+VDC)
VBUS: IC2.7 (VBUS), JP3.3, T1.1 (D), X3.VBUS
VCC-ISO: B1.5V_ICSP (VCC), C3.1, C5.2, IC2.6 (UCAP), IC2.14 (VCC), IC2.24 (AVCC), IC2.33 (PE2(!HWB)), IC2.34 (VCC1), IC2.44 (AVCC1), J1.1, J1.4, J1.7, J1.10, J1.13, J1.16, J2.1, J2.4, J2.7, J2.10, J2.13, J2.16, SJ1.2, U5.19 (VCCB)
VCCA: C9.1, C10.1, C25.1, C37.1, L2.2, R19.2, R20.2, U4.4 (AVDD), U4.8 (AVDD), U4.11 (AVDD), U4.15 (AVDD), U4.17 (AVDD), U4.21 (AVDD)
WIZ_RST: IC2.22 (PD5(XCK/CTS)), U5.15 (B5)
WIZ_RST_WIZ: R9.1, U4.37 (RST_N), U5.6 (A5)

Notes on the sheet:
W5500 Subsystem
W5500 VCCA Filter
FEATHER WING
POWER AND FILTERING
VBAT = PoE V+
VOLTAGE SELECT (3.3V DEFAULT)
PoE Ethernet Jack
UNO SHIELD
3V LOGIC BUFFER
ATMEGA32U4
POWER SUPPLY: 5V
POWER SUPPLY SELECTION
VBAT is POE Voltage
VBAT = PoE Unit Power VCC-ISO = Logic Level Vcc
